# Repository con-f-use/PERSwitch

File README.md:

The files that came with this readme are part of the PERSwtich USB power swtich
project. It is a simple free electronics project based on an AtTiny26
(or similar) microcontroller.

For more details see the Documentation in the ./docu directory of this program.

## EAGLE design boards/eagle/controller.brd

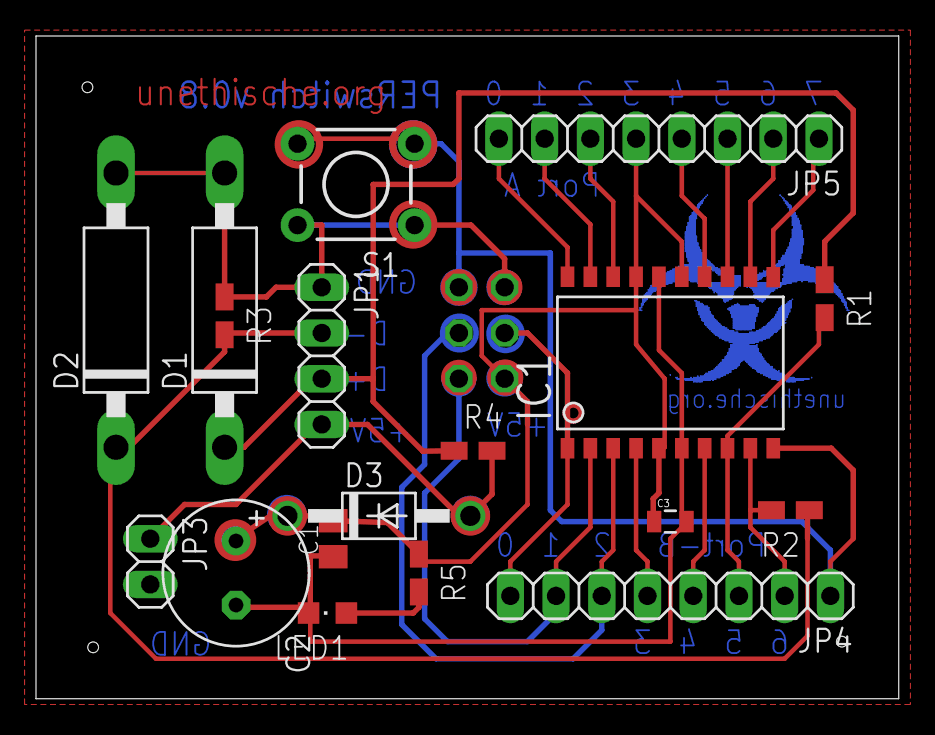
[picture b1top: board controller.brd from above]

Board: 2 copper layers, 47.9 x 36.8 mm, 20 parts (1 on the bottom side), 21 nets.

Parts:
C1: 100nF; C0805K
C2: 10uF; E3,5-8
C3: 10nF; 0805
D1, D2: 3V6; C1702-15
D3: 1N4004; DO41-10
IC1: TINY26LS; SO20L
JP1: USB; 1X04
JP2: ISP; 2X03
JP3: POWER; 1X02
JP4: Port B; 1X08
JP5: Port A; 1X08
LED1: CHIPLED_0805
R1, R2: 68 Ohm; R0805W
R3: 1M Ohm; R0805W
R4, R5: 1k5 Ohm; R0805W
S1: TACTILE-PTH
U$1: UNETHILOGO

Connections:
+5V: C1.2, C2.+, C3.1, D3.C, IC1.5, IC1.15, IC1.17, JP2.2, JP5.5, R5.1
D+: IC1.9, JP4.2, R2.2
D+RAW: D2.C, JP1.2, R2.1, R3.2
D-: IC1.8, JP4.3, R1.2
D-RAW: D1.C, JP1.3, R1.1, R4.1
GND: C1.1, C2.-, C3.2, D1.A, D2.A, IC1.6, IC1.16, JP1.1, JP2.6, JP3.2, LED1.C, R3.1, S1.1, S1.2
MISO: IC1.2, JP2.1, JP4.7
MOSI: IC1.1, JP2.4, JP4.8
unnamed: LED1.A, R5.2
unnamed: IC1.7, JP4.4
unnamed: IC1.4, JP4.5
unnamed: IC1.20, JP5.8
unnamed: IC1.11, JP5.1
unnamed: IC1.12, JP5.2
unnamed: IC1.13, JP5.3
unnamed: IC1.14, JP5.4
unnamed: IC1.18, JP5.6
unnamed: IC1.19, JP5.7
RST: IC1.10, JP2.5, JP4.1, S1.3, S1.4
SCK: IC1.3, JP2.3, JP4.6
VCC: D3.A, JP1.4, JP3.1, R4.2

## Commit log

2015-07-22 Initial commit v0.8
2017-07-31 USB warnings & generous matching vendor/device
    ToDo: Make this a compile time option (e.g. -DDEBUG).
2020-10-31 package for nix with libusb-compat
2020-11-08 make perscom default target
2020-11-08 move default.nix and add gitignore
2020-11-08 fix compat issue with nixos configs (hopefully)
2020-12-03 cleanup perscom.nix
2020-12-03 perscom.nix: missing semicolon
2021-12-04 nix: remove deprecated stdenv.lib
2021-12-04 nix: missing lib
